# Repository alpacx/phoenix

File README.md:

# Phoenix — gateway multi-piattaforma

Gateway sperimentale, non ancora un prodotto validato. Backend ESP32 esistente;
backend Linux per ROCK 4C+ implementato in forma sperimentale e testato in Docker. La sezione hardware/build sotto descrive
ESP32; per Linux consultare il relativo README e le verifiche disponibili.

## Organizzazione

- [ESP32 / ESP-IDF](platforms/esp32/README.md): sorgenti in `platforms/esp32/main/`.
- [Linux / ROCK](platforms/linux/README.md): backend Linux, istruzioni e stato delle verifiche.
- `shared/web/`: pannello amministrativo comune.
- `shared/phoenix_core/`: logica C portabile.
- [Mappa del progetto](docs/PROJECT_STRUCTURE.md) e [istruzioni agenti](AGENTS.md).
- `hardware/phoenix-g1/`: progettazione della scheda custom, ancora incompleta.

Implementati: Ethernet IP101/RMII con DHCP, USB HS CDC-NCM con DHCP/NAT IPv4,
firewall L3/L4, API amministrativa locale e pannello, importatore WireGuard IPv4
full tunnel e blocco in uscita, gestione C6 STA/AP e aggiornamento firmato in software. La presenza del codice e una build riuscita non
provano il funzionamento sul banco: consultare PROGRESS.md.

## Build

ESP-IDF 5.5.4, commit esatto `10ca0dff2f40aeb539f22d1ef88d031cf7421743`.
Dipendenze registry e relativi hash in dependencies.lock. Toolchain installata:
`riscv32-esp-elf esp-14.2.0_20260121`. Script configurato per l'ambiente locale;
IDF_PATH e IDF_PYTHON_ENV_PATH sono sovrascrivibili.

```sh
./tools/test.sh
# Scheda rilevata v3.1; USB dati spento:
./tools/build.sh -B build-rev3 -D SDKCONFIG=build-rev3/sdkconfig \
  -D 'SDKCONFIG_DEFAULTS=sdkconfig.defaults;sdkconfig.rev3'
# Solo compilazione del percorso USB, NON certifica il cablaggio:
./tools/build.sh -B build-usb-rev3 -D SDKCONFIG=build-usb-rev3/sdkconfig \
  -D 'SDKCONFIG_DEFAULTS=sdkconfig.defaults;sdkconfig.rev3;sdkconfig.lab;sdkconfig.signed'
```

La variante firmata richiede prima la chiave descritta in [OTA](docs/OTA.md).

Il default sdkconfig.defaults supporta P4 v1.x; non caricarlo sulla v3.1.
Per una build USB di banco v3.x aggiungere sdkconfig.lab DOPO sdkconfig.rev3
in una cartella di build nuova. Non modificare i file SDK globali.

## Cablaggio e flash

Leggere [HARDWARE.md](docs/HARDWARE.md). La USB-C è seriale/alimentazione; la
Type-A è OTG e porta VBUS generata dalla scheda. Non collegare un generico
cavo host-host. USB dati resta disattivata per default.

Il backup originale è locale, riservato e ignorato da Git:
`results/recovery/original-flash.bin`. Non distribuirlo: può contenere dati
preesistenti. Per ripristinare, dopo aver identificato nuovamente la stessa
scheda e verificato hash/dimensione:

```sh
# Da ambiente ESP-IDF attivato. PORT deve essere la P4 dedicata identificata.
python -m esptool --chip esp32p4 --port "$PORT" write_flash 0 results/recovery/original-flash.bin
```

Non modificare eFuse. Nessuna flash encryption/secure boot irreversibile attivata.
BOOT+RESET è la via ROM di recupero; BOOT condivide GPIO35 con Ethernet TXD1:
non usarlo come pulsante dell'interfaccia durante il traffico.

## Uso sperimentale

USB LAN: 192.168.7.1/24, DHCP, pannello http://192.168.7.1/. Nessun servizio
amministrativo accettato dall'uplink. Pairing via UART nei primi 120 secondi:
`pair ` seguito da 64 caratteri esadecimali casuali, mai riportati nei log.
Il token rimane solo nel client; la scheda conserva SHA-256 in NVS.
`time <epoch UNIX di 10 cifre>` imposta l'orologio nello stesso intervallo.
Il pannello conserva il token nella sessionStorage della scheda browser e lo elimina al logout.

All'avvio il traffico inoltrato è bloccato. La modalità diretta è una scelta
esplicita via API. WireGuard resta chiuso finché non esiste una sessione valida.
Il dispositivo non controlla il traffico del Mac sulle altre interfacce.
Non è un antivirus, un IDS completo o uno strumento di ispezione HTTPS.

[API](docs/API.md) · [Architettura](docs/ARCHITECTURE.md) ·
[Prove](docs/TESTING.md) · [Dipendenze](docs/DEPENDENCIES.md) ·
[Attività](TASKS.md) · [Ripresa](NEXT_SESSION.md)

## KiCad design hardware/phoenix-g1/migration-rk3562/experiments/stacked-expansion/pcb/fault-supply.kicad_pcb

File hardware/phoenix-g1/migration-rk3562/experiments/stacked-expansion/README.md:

# Espansione sovrapposta — sostituzione J3

Stato: **schema integrato, piazzamento e blocco locale di protezione parzialmente instradati e verificati**.
Il derivato corrente è indicato da `working-candidate.json`.
Non pronto per fabbricazione. Il checkpoint precedente `../lpddr4-1gb/working-board.json`
resta immutato; questo candidato va completato prima di promuoverlo.

## Fissaggi obbligatori — riserva CAD

Aprire `mechanical/mounting-reservations.kicad_pcb`, layer **Dwgs.User**:
H8101 (53;4) e H8102 (83;3) mm, due posizioni asimmetriche rispetto a J3.
Cerchio interno: futuro foro NPTH 2,2 mm per M2; esterno: riserva 5,4 mm
su entrambi i lati per testa vite/distanziale e margine. Distanza PCB nominale
3,5 mm, da abbinare alle tolleranze DF40; nessun distanziale commerciale
ancora selezionato. La coppia di fori da sola non certifica l'anti-inversione.

**Non sono fori già realizzati**: l'overlay segnala le riserve e non genera
forature. Per liberarle vanno ricollocati C422/C425/R1811 presso H8101 e
C445/C470/L405/R431 presso H8102. Nessuna pista/via esistente attraversa
le riserve nella verifica geometrica attuale. Zone rame da tenere escluse
quando si creeranno i fori. `mechanical/mounting-interface.json` registra
questi blocchi: risolverli è obbligatorio prima del rilascio e prima di
progettare la figlia. Riconvalidare tutto nel passaggio a 85×35 mm.
Rigenerare l'overlay con `tools/reserve_stacked_mounts.py` dopo ogni
variazione del candidato. Il PCB elettrico precedente resta invariato.

## Scelta e posizione

J3 sostituisce il precedente PZ127 2×10: non aggiunge un secondo connettore.
Base Hirose DF40C-40DP-0.4V(51), JLC C424643; controparte sulla futura
scheda accessoria DF40HC(3.5)-40DS-0.4V(51), JLC C3020022.
40 contatti a passo 0,4 mm, distanza nominale tra PCB 3,5 mm.
Corpo base 9,52×2,97 mm; courtyard 10,1×3,9 mm.
Centro sul PCB: (67,5; 2,5) mm, lato superiore, vicino a Ethernet.
Tre condensatori non instradati (C423/C431/C435) passano al retro alle stesse
coordinate. La qualità del loro futuro collegamento di alimentazione resta da verificare.
Il PCB candidato conserva **90×40 mm**; il target **85×35 mm** non è ancora validato.

Il connettore non è polarizzato: servono fissaggi asimmetrici o una chiave
meccanica. La scheda figlia deve evitare il corpo RJ45 e lasciare spazio al
raffreddamento passivo; 3,5 mm NON autorizzano una scheda piena sopra tutti i
componenti. Sagoma, fissaggi, altezza totale e assemblabilità da verificare.

## Interfaccia

`pinout.json` definisce la numerazione custom Phoenix, non uno standard HAT.
USB 2 host dedicata RK3562: AE26 DM e AE27 DP; USB-C device invariata.
Sono disponibili I2C, UART, SPI e quattro GPIO a logica 3,3 V.
GPIO0 abilita l'alimentazione; GPIO1 legge il fault. Due contatti restano NC.
Il modem, la eSIM, i regolatori e l'eventuale adattamento livelli sono sulla
scheda accessoria futura: non sono inclusi in questo progetto.

Otto contatti portano +5V_ADDON, ma la corrente nominale di 0,3 A per contatto
non dimostra un budget di sistema di 2,4 A. Il ramo TPS259531 è disabilitato
all'avvio tramite pull-down e ha un limite preliminare di circa 0,99 A.
Il budget USB d'ingresso deve alimentare anche tutta la scheda base: non è
ancora dimostrato che basti per un modem LTE, soprattutto nei picchi.
Non collegare a caldo e non alimentare esternamente la scheda accessoria.
MP1–MP4 sono soli ancoraggi meccanici. La controparte richiede verifica della
corrispondenza speculare dei contatti prima del layout della scheda figlia.

## Evidenze e costi

Snapshot JLC in `sourcing/`, osservati il 13 novembre 2026:
- C424643: canPresaleNumber 12913, prezzo iniziale 0,5367 USD.
- C3020022: canPresaleNumber 1991, prezzo iniziale 1,1518 USD.
Totale indicativo coppia 1,6885 USD; non include PCBA, spedizione, imposte,
protezione di alimentazione né scheda figlia. I campi di stock non si sommano
tra loro e non garantiscono disponibilità immediata per un ordine PCBA.

Dimensioni dal catalogo Hirose locale `hirose-df40-catalog.pdf`, pagine 7 e 10;
[scheda ufficiale base](https://www.hirose.com/en/product/p/CL0684-4013-7-51).
Footprint con numerazione Phoenix: da qualificare con i componenti reali.
La regola DRC da 0,17 mm vale SOLO fra pad dello stesso J3 (passo 0,4 mm,
land 0,23 mm), senza ridurre la clearance generale.

`audit.json`: 71 disposizioni pin schema/PCB verificate; 2460 segmenti/via
preservati; UUID distinti; reti originali invariate salvo i due pin host prima NC.
DRC: nessun corto/clearance/courtyard aggiuntivo; restano 125 via dangling e
14 problemi serigrafia preesistenti. 499 elementi non connessi riportati:
possibile limite di report, non misura del totale residuo.
ERC: 15 power_pin_not_driven e una isolated_pin_label; NON pulito.

## Lavoro ancora necessario

Instradare USB host a impedenza controllata e ramo di alimentazione; qualificare
protezione ESD, dissipazione e picchi del modem; assegnare MPN ai passivi nuovi
ed aggiornare disponibilità del ramo di potenza. Integrare separatamente eMMC,
display e comando, poi compattare sul target. Progettare controparte, chiave
meccanica e fissaggi prima di ordinare. Nessuna simulazione SI/PI o prova fisica.

## Riproduzione

1. `tools/build_stacked_expansion.py` con Python + sexpdata.
2. Esportare `system/kicad/integrated/phoenix-g1.kicad_sch` con KiCad CLI
   `sch export netlist --format kicadxml` in `system/review/netlist.xml`.
3. `tools/place_stacked_expansion.py` con Python KiCad pcbnew.
4. KiCad CLI `pcb drc --format json` in `pcb/drc.json` e
   `sch erc --format json` in `system/review/erc.json`.
5. `tools/audit_stacked_expansion.py` con Python KiCad pcbnew.

Gli script riscrivono solo questa directory candidata; non il PCB sorgente.

## Riserve ausiliarie H8103–H8105

Aggiunti tre punti M2 provvisori, oltre ai due della scheda figlia, nel medesimo
overlay `mechanical/mounting-reservations.kicad_pcb` (Dwgs.User).
La mappa `mechanical/mounting-overview.svg` mostra la distribuzione proposta.
- H8103 (21;3): staffa/case lato USB.
- H8104 (37;31): possibile staffa per dissipazione; interferisce con clock,
  test point e condensatori. Priorità all'integrità elettrica: spostare la
  riserva anziché il clock se il successivo layout lo richiede.
- H8105 (70;34): appoggio staffa/case lato Ethernet.

Riserve da 5,4 mm, futuro NPTH 2,2 mm; nessuna foratura reale introdotta.
21 riferimenti interferiscono con le tre nuove riserve, censiti nel JSON.
Il controllo geometrico non trova piste/via nelle riserve, ma le zone rame
non sono escluse e le quote devono essere riconvalidate dopo la compattazione.
Non è un fissaggio diretto standard per una ventola: servirebbe una staffa
adattatrice. Non è stato aggiunto un circuito elettrico per alimentarla.
Raffreddamento passivo prioritario. Evitare carico concentrato sul BGA,
verificare flessione PCB, pressione del thermal pad, isolamento e accesso viti.
I 3,5 mm della scheda figlia non definiscono l'altezza delle staffe ausiliarie.

## Avanzamento collegamenti locali — checkpoint corrente

Ripartire da `working-candidate.json`: `pcb/logic-reference.kicad_pcb`, verificato
in `pcb/logic-reference-audit.json`. Il PCB principale LPDDR4 rimane invariato.

- Riposizionati i sei passivi U8101, senza cambiare netlist o componenti.
- Tutte e quattro le reti locali ILIM/dVdt/EN/fault collegate ai rispettivi
  passivi; dVdt accorciata da 7,79 a 2,83 mm.
- Sette pad GND collegati al piano esistente, continuità verificata fino a
  U4.69; altri pin GND del PMIC restano incompleti nel progetto generale.
- Collegati i due pin IN al condensatore di ingresso e OUT al condensatore
  di uscita. Tracce locali 0,3 mm: non è una qualifica di portata/temperatura.
- R8102.2 collegata alla linea +3V3_IO U4.55 con un nuovo via e percorso
  interno In2.Cu. Continuità verificata, 14,81 mm nominali di percorso.
- 2460 piste/via originali preservati, 114 nuovi segmenti/via nel derivato.
- DRC invariato: 125 via dangling e 14 difetti serigrafia preesistenti,
  nessun nuovo corto/clearance/courtyard. 499 airwire riportati, conteggio
  potenzialmente limitato. Non significa completamento della scheda.

Restano alimentazione d'ingresso del ramo, uscita verso J3, GPIO fino al SoC,
coppia USB, budget energetico e qualifica elettrica/termica. I fissaggi
restano riserve non liberate; eMMC/display/comando e compattazione sono aperti.
I render precedenti non rappresentano questo ultimo piazzamento.

Catena riproducibile (Python KiCad): `route_stacked_control.py`,
`route_stacked_ground.py` (con --input/--output/--report),
`route_stacked_local_power.py`, `route_stacked_fault_supply.py`.
Eseguire DRC sul risultato e `audit_stacked_local_power.py fault-supply`.
Gli output intermedi mantengono i rispettivi limiti e non sono checkpoint finali.

Il tentativo `mechanical/mount-clearance-trial.kicad_pcb` è SCARTATO:
spostava troppo lontano alcuni passivi di potenza e non liberava due componenti.
Non usarlo come base di routing. Le riserve restano nel relativo overlay.

## Vincoli USB e fabbricazione

La [guida ufficiale JLCPCB](https://jlcpcb.com/help/article/user-guide-to-the-jlcpcb-impedance-calculator),
consultata il 13 novembre 2026, lega il calcolo a stack-up, strato, riferimento,
rivestimento e geometria. Il record JLC06161H-3313 del progetto è ancora un
candidato: non definisce larghezza/gap USB qualificati. Il tentativo di usare
il calcolatore interattivo è impedito dal browser host non disponibile in
questa sessione. Non sono stati inventati o applicati valori di impedenza.

## Avanzamento successivo: alimentazione e controlli fino a J3

Il derivato `logic-reference` completa geometricamente:
- ingresso eFuse dalla rete +5V_MAIN esistente;
- uscita eFuse agli otto contatti +5V_ADDON di J3;
- quattordici contatti GND J3 al piano esistente;
- abilitazione e fault U1.K2/U1.L3 ↔ J3.27/J3.28 ↔ eFuse;
- riferimento +3V3_IO al contatto J3.36.

R8102 ora ruotata di 180° per separare l'uscita fault dal suo pull-up.
747 segmenti/via nuovi rispetto al candidato originario; tutti i 2460
precedenti preservati. DRC resta alle stesse 139 violazioni preesistenti.
Collegamento non equivale a qualifica di portata: alimentazione interna
1 mm su In3, colli esterni 0,3 mm, via 0,6/0,3 mm e dita J3 0,15 mm sono
candidati con verifica termica/caduta/tolleranze e budget USB ancora aperti.
La corrente nominale del limite di protezione non è un budget di carico LTE.

Regole aggiunte, esplicite nei .kicad_dru: 0,17 mm di clearance solo contro
pad J3; 0,15 mm di larghezza minima per dita +5V_ADDON; 0,0762 mm per
escape GPIO dal BGA. Le piste lontane dal connettore conservano 0,20 mm di
clearance. Escape BGA vincolati al processo sperimentale già usato dalla DDR:
nessuna qualifica di fabbricazione o integrità del segnale implicita.
Istruzioni precedenti che descrivono feed/GPIO aperti sono storiche.

## Riserve meccaniche applicate al rame

`protect_stacked_mounts.py` genera `pcb/mount-protected.kicad_pcb` da cui
riparte la catena di routing. H8101–H8105 sono rule area su tutti e sei gli
strati: vietati nuove piste, via e riempimenti. I componenti che occupano
le riserve sono ancora da ricollocare; i fori non sono creati. Le rule area
non vietano pad/footprint esistenti, per distinguere quel lavoro irrisolto
dalla protezione del nuovo routing.

Il checkpoint `logic-reference` è stato rigenerato con tali zone: tutti i
controlli end-to-end passano, DRC invariato. Nel piazzamento aggiornato C8103
è (79;4,2) mm/180°, R8103 (82,5;9,5) mm/0°, R8102 (73;6,5) mm/180°.
Il report JSON attuale prevale sui conteggi e sulle coordinate storiche.

`tools/rebuild_stacked_expansion.py` ricostruisce i passaggi in sequenza,
interrompendosi su fallimento del tool o nuove violazioni DRC; promuove il
checkpoint solo dopo la verifica di tutte le connessioni richieste e delle
cinque riserve. Lo stadio intermedio output-bus ammette un via dangling
aggiuntivo, che deve scomparire allo stadio output-feed.

`tools/route_stacked_aux_io.py` è un esperimento separato: ogni rete viene
accettata soltanto dopo continuità e DRC; le altre vengono scartate. Non
qualifica SPI/UART/I2C né il processo delle piste BGA a 3 mil, e non
completa la coppia USB. L'audit finale deve precedere la promozione.

## Checkpoint 13 novembre — segnali ausiliari e riserve meccaniche

Il puntatore `working-candidate.json` ora seleziona `pcb/aux-io.kicad_pcb`.
L'audit preserva tutte le 2.460 piste/via originali e le reti dei pad; aggiunte
1.591 primitive, non 1.591 reti. Le 139 violazioni DRC preesistenti sono invariate.
Cinque riserve meccaniche impediscono nuove piste/via/riempimenti, ma non sono
fori reali e contengono ancora componenti da riposizionare.

Alimentazione protetta, masse, riferimento logico e GPIO enable/fault sono
collegati. Dei segnali aggiuntivi risultano collegati SCL, SPI_CLK, MOSI, CS0.
SDA, MISO, CS1, UART TX/RX e GPIO2/3 restano aperti; USB non instradata.
I tentativi `aux-io-second` e `aux-io-fine` non hanno aggiunto percorsi e non
sostituiscono il checkpoint. La ricerca limitata non dimostra impossibilità
fisica: occorre rivedere il fanout completo del connettore, evitando di occupare
prima i corridoi necessari ai pad adiacenti.

`rebuild_stacked_expansion.py` ricostruisce fino a `logic-reference` e riporta
il puntatore a quel livello. Per riprodurre lo stadio successivo eseguire
`route_stacked_aux_io.py`, quindi `audit_stacked_local_power.py aux-io` con
Python KiCad; promuovere soltanto dopo controllo del report e SHA.
Il candidato eMMC è separato in `../emmc-system`: schema aggiornato, PCB ancora
con NOR. Non utilizzare netlist e PCB dei due candidati come coppia di produzione.

Studio meccanico `mechanical/mount-local-trial.json`: ricerca di spostamenti
entro 4 mm sullo stesso lato; solo R1811 trova una posizione libera, senza nuovi
DRC. Gli altri sei componenti presso H8101/H8102 richiedono una revisione locale
più ampia. Studio non promosso; nessun foro creato.

Il tentativo `aux-io-wide` non è promosso: nella versione sperimentale del
selettore di strato mancava In3 dalla verifica delle via. Il DRC ha respinto
il percorso e preservato il checkpoint; il generatore ora verifica sempre
i sei strati distinti, indipendentemente dallo strato di routing scelto.

## Inventario senza limite del report DRC

`inventory_stacked_connectivity.py` usa la connettività dei pad, senza affidarsi
al limite degli elementi mostrati dal DRC. Sul checkpoint aux-io: 276 reti,
269 reti con più pad,231 reti ancora suddivise in gruppi. GND ha 582 pad e 471 gruppi.
Il report è `pcb/connectivity-inventory.json`, legato allo SHA del PCB.
Questi numeri non sono percentuali di completamento né qualifiche elettriche.

Anche i tentativi conclusivi `aux-io-back` e `aux-io-small-via` non hanno
aggiunto reti: il secondo usa via 0,45/0,20 mm entro le regole esistenti.
L'audit finale conferma il checkpoint precedente, senza nuove violazioni.
Non ripetere questi tentativi invariati: occorre modificare la disposizione
delle uscite del connettore o il relativo fanout, poi ripetere i controlli.

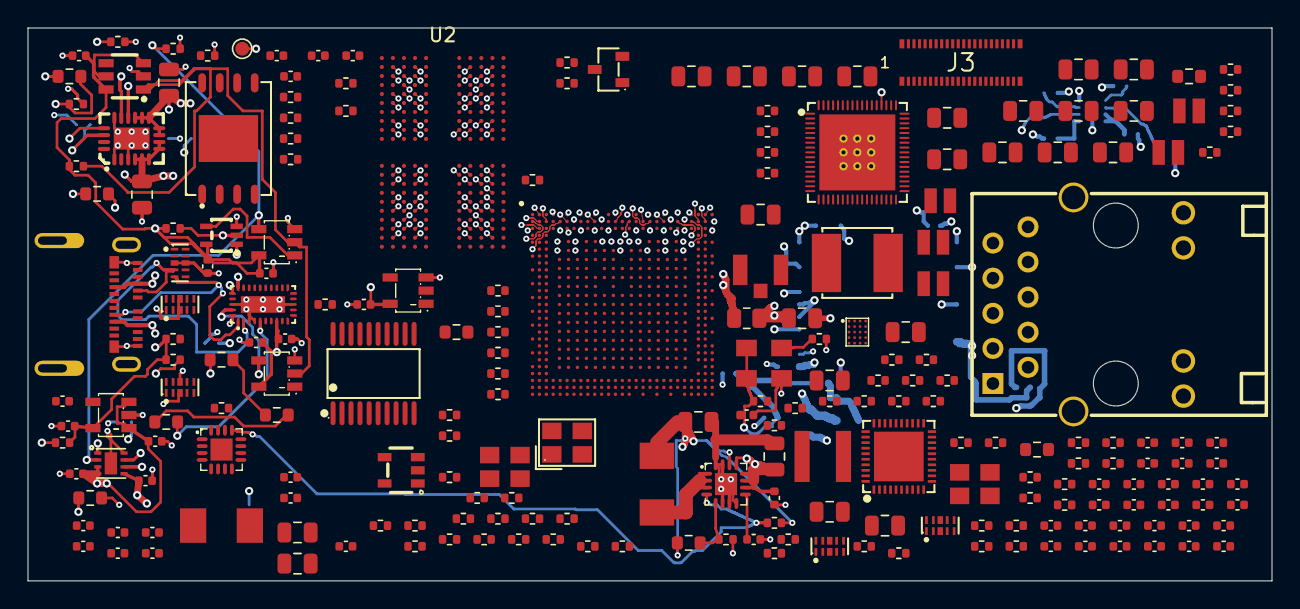
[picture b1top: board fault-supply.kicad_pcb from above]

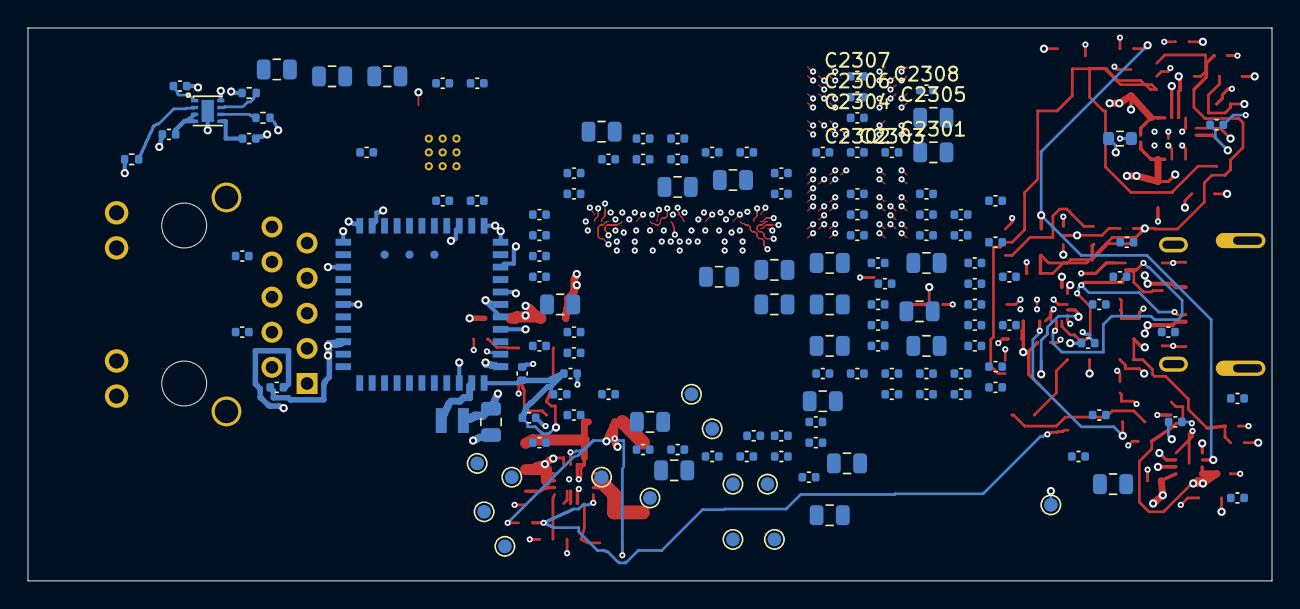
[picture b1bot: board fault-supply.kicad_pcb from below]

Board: 6 copper layers, 90.0 x 40.0 mm, 362 parts (141 on the bottom side), 268 nets.

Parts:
C410, C411, C412, C451, C452, C454, C501, C512, C513, C514, C516, C517, C518, C522, C1103, C1104, C1105, C1106, C1107, C1401, C1503, C1811, C2007, C2302, C2303, C2304, C2306, C2307, C2308: 100n; C_0402_1005Metric
C413, C414, C415, C519, C1402, C8101, C8102: 1u; C_0402_1005Metric
C421, C422, C423, C424, C425, C431, C432, C433, C434, C435, C441, C442, C443, C444, C445, C1304, C1305, C1603, C1604, C1605, C1606, C1607, C1608, C1613, C1614, C1618, C1619, C1622, C1623, C2204: 22u / 10V; C_0805_2012Metric
C460, C461, C462, C463, C464, C465, C466, C467, C468, C469, C480, C481, C482, C483, C484, C485, C531, C1101, C1201, C1203, C1611, C1612, C1626, C1628, C1630, C1632, C1634, C1636, C1680, C1682, C1801, C1812, C2005: 1u / 10V; C_0402_1005Metric
C470, C1301, C1615, C1620, C1624, C1650, C1664, C1678, C2201: 10u / 10V; C_0805_2012Metric
C511, C515: 4.7u; C_0402_1005Metric
C520, C521, C1501, C1502: 20p C0G / tune; C_0402_1005Metric
C601, C602, C603, C604, C605: 100n / 16V X7R; C_0402_1005Metric
C606: 100n / 10V X7R; C_0402_1005Metric
C1001, C1002, C1011, C1012, C1013, C1014: 22u / 10V X5R; C_0805_2012Metric
C1020: 1u / 10V X5R; C_0402_1005Metric
C1102, C1802: 2.2u / 10V; C_0402_1005Metric
C1202: 22n / 10V; C_0402_1005Metric
C1302, C1601, C1609, C1616, C1621, C1625, C1627, C1629, C1631, C1633, C1635, C1637, C1638, C1639, C1640, C1641, C1642, C1643, C1644, C1645, C1646, C1647, C1651, C1652, C1653, C1654, C1655, C1656, C1657, C1658, C1659, C1660, C1661, C1662, C1665, C1666, C1667, C1668, C1669, C1670, C1671, C1672, C1673, C1674, C1675, C1676, C1679, C1681, C1683: 100n / 10V; C_0402_1005Metric
C1303: 10n / 10V; C_0402_1005Metric
C1602, C1610, C1617, C1648, C1649, C1663, C1677: 4.7u / 10V; C_0402_1005Metric
C1901, C1902: 1u / 25V X7R; C_0805_2012Metric
C1903: 1n / C0G; C_0402_1005Metric
C2001: 22u / 6.3V; C_0805_2012Metric
C2002, C2006, C2202: 100n / 16V; C_0402_1005Metric
C2003: 4.7u / 6.3V; C_0805_2012Metric
C2004: 4.7u / 6.3V; C_0402_1005Metric
C2008, C2009: 8p C0G; C_0402_1005Metric
C2203: 1n / 10V; C_0402_1005Metric
C2301, C2305: 10u; C_0805_2012Metric
C8103: 22n; C_0402_1005Metric
FB2001: 100R @100MHz / 4A; R_0805_2012Metric
J1: 2012670005; USB_C_Molex_2012670005
J2: HR911130A; RJ45-TH_HR911130A
J3: DF40C-40DP-0.4V(51); DF40C_40DP_0.4V
J2001: U.FL-R-SMT-1; Hirose_UFL_R_SMT_1_80
L401, L402, L403, L404, L405: 470nH; L_APH201610
L501: 2.2uH DCR39m max; L_ANR4030
L1001: 240nH - candidate; IND-SMD_L5.0-W5.0-PRS5020-330MT
L1301, L2201: 2.2uH DCR35m max; L_APH0518
L2001: 2.2uH / 2.4A Isat at 20C; Murata_DFE201610E
Q1: MMBT3904-C20526; SOT-23-3_L2.9-W1.3-P1.90-LS2.4-BR
R201: 240R 1%; R_0402_1005Metric
R410: 180k 1%; R_0402_1005Metric
R411, R1505, R2203: 100k 1%; R_0402_1005Metric
R412, R413, R516, R1402, R1403, R1404, R1504, R2002: 10k; R_0402_1005Metric
R414, R415, R501, R502, R503, R504, R505, R506, R507, R508, R509, R510, R511, R512, R515, R1401, R1501, R2003: 22R; R_0402_1005Metric
R416, R417: 2.2k; R_0402_1005Metric
R421, R422, R424, R2004: 100R; R_0402_1005Metric
R431: 45.3k 0.1%; R_0603_1608Metric
R432: 121k 0.1%; R_0603_1608Metric
R513: 2.49k 1%; R_0402_1005Metric
R514: 1.8k; R_0402_1005Metric
R521, R522, R523, R524, R525, R526, R527, R528, R529, R2101, R2102: 4.7k; R_0402_1005Metric
R530: 0R - power link; R_0402_1005Metric
R601, R605, R606: 300k 0.1% 25ppm; R_0603_1608Metric
R602, R603, R604: 200k 1%; R_0402_1005Metric
R1001: 100R 1%; R_0402_1005Metric
R1002: 51k 1%; R_0402_1005Metric
R1101, R1103, R1202, R1301, R1804, R2201, R8102, R8103: 100k; R_0402_1005Metric
R1102, R1802, R1811, R1812, R1813, R1814, R1815, R2010, R2011, R2012, R2013, R2014, R2103, R2104: 47k; R_0402_1005Metric
R1201: 806R 1%; R_0603_1608Metric
R1502: 1M; R_0402_1005Metric
R1503: 120R 1%; R_0402_1005Metric
R1506: 1M 1%; R_0402_1005Metric
R1507: 0R; R_0402_1005Metric
R1601, R1602: 0R supply link; R_0402_1005Metric
R1801: 1k; R_0402_1005Metric
R1803: 180R 1%; R_0603_1608Metric
R1901: 35.7k 0.1% 25ppm; R_0603_1608Metric
R1902, R1904: 10k 0.1% 25ppm; R_0402_1005Metric
R1903: 47.5k 0.1% 25ppm; R_0603_1608Metric
R1905: 33.2k 1%; R_0603_1608Metric
R2001: 0R RF tuning; R_0402_1005Metric
R2202: 348k 1%; R_0603_1608Metric
R8101: 2.1k candidate; R_0402_1005Metric
TP1: GND; TestPoint_Pad_D1.0mm
TP2: VBUS_RAW; TestPoint_Pad_D1.0mm
TP3: +5V_MAIN; TestPoint_Pad_D1.0mm
TP4: +3V3_SYS; TestPoint_Pad_D1.0mm
TP5: +3V3_PMU; TestPoint_Pad_D1.0mm
TP6: +3V3_IO; TestPoint_Pad_D1.0mm
TP7: +1V5_DDR; TestPoint_Pad_D1.0mm
TP8: VDD_CPU; TestPoint_Pad_D1.0mm
TP9: RESET_N; TestPoint_Pad_D1.0mm
TP10: RECOVERY_ADC; TestPoint_Pad_D1.0mm
TP11: DEBUG_RX; TestPoint_Pad_D1.0mm
TP12: DEBUG_TX; TestPoint_Pad_D1.0mm
TP13: USB_POWER_FAULT_N; TestPoint_Pad_D1.0mm
TP14: SYS_3V3_PG; TestPoint_Pad_D1.0mm
U1: RK3562; RK3562_FCCSP478_13.9mm_MIXED_PITCH_CANDIDATE
U2: H9HCNNN8KUMLHR-NME; H9HCNNN8KUMLHR_FBGA200_10x15_P0.8x0.65_DRAFT
U4: RK809-5; QFN-68_L7.0-W7.0-P0.35-BL-EP5.5
U5: RTL8211F-CG; WQFN-40_L5.0-W5.0-P0.4-BL-EP
U6: HD3SS3220IRNHR; WQFN-30_L4.5-W2.5-P0.4-BL-EP
U7, U8, U9: TPD4EUSB30DQAR; USON-10_L2.5-W1.0-P0.50-BL
U10: RK860-0; WLCSP-20_L2.0-W1.6-R5-C4-P0.40-TL
U11: TLV75533PDBVR; SOT-23-5_L3.0-W1.7-P0.95-LS2.8-BR
U12: TPS3808G33DBVR; SOT-23-6_L2.9-W1.6-P0.95-LS2.8-BR
U13, U16: SN74LVC1G04DBVR; SOT-23-5_L3.0-W1.7-P0.95-LS2.8-BR
U14: SN74LVC1G02DCKR; SC-70-5_L2.1-W1.3-P0.65-LS2.1-BR
U15, U8101: TPS259531DSGR; WSON-8_L2.0-W2.0-P0.50-TL-EP
U17: TPS62132RGTR; VQFN-16_L3.0-W3.0-P0.50-TL-EP
U18: W25Q256JVEIQTR; WSON-8_L8.0-W6.10-P1.27-BL-EP
U19: SN74LVC1G08DBVR; SOT-23-5_L3.0-W1.7-P0.95-LS2.8-BR
U20: TPS7A2030PDBVR; TSOT-23-5_L2.9-W1.6-P0.95-LS2.8-BR
U21: SN74LVC541APWR_C113281; TSSOP-20_L6.5-W4.4-P0.65-LS6.4-BL
U22, U23: TPD4E05U06DQAR; USON-10_L2.5-W1.0-P0.50-BL
U24: TPS25940ARVCR; WQFN-20_L4.0-W3.0-P0.50-BL-EP
U25: AP6256; AP6256_12x12_P0.9
U26: TPS62130RGTR; VQFN-16_L3.0-W3.0-P0.50-TL-EP
Y1: 24MHz CL12pF ESR40R; Crystal_3225_JWT
Y501: 25MHz CL12pF; Crystal_3225_YXC
Y2001: OVETDLJANF-32.768KHZ; Taitien_OV_5032
Y2002: X1E0000210877; CRYSTAL-SMD_4P-L3.2-W2.5-BL

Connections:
+1V0_PHY: C511.1, C512.1, C513.1, C514.1, C522.1, L501.2, U5.3, U5.8, U5.21, U5.38
+1V1_LPDDR4: C433.1, C443.1, C1646.1, C1647.1, C1648.1, C1649.1, C1650.1, C1651.1, C1652.1, C1653.1, C1654.1, C1655.1, C1656.1, C1657.1, C1658.1, C1659.1, C1660.1, C1661.1, C1662.1, C1663.1, C1664.1, C1665.1, C1666.1, C1667.1, C1668.1, C1669.1, C1670.1, C1671.1, C1672.1, C1673.1, C1674.1, C1675.1, C1676.1, C1677.1, C1678.1, L403.2, R201.2, R431.1, R1503.2, TP7.1, U1.1D6, U1.1D11, U1.1E3, U1.1E4, U1.1E5, U1.1E6, U1.1E7, U1.1E8, U1.1E9, U1.1E10, U2.A4, U2.A9, U2.AA3, U2.AA5, U2.AA8, U2.AA10, U2.AB4, U2.AB9, U2.B3, U2.B5, U2.B8, U2.B10, U2.D1, U2.D5, U2.D8, U2.D12, U2.F3, U2.F5, U2.F8, U2.F10, U2.G2, U2.H1, U2.H5, U2.H8, U2.H12, U2.K1, U2.K3, U2.K10, U2.K12, U2.N1, U2.N3, U2.N10, U2.N12, U2.R1, U2.R5, U2.R8, U2.R12, U2.T2, U2.U3, U2.U5, U2.U8, U2.U10, U2.W1, U2.W5, U2.W8, U2.W12, U4.26
+1V8_SYS: C435.1, C445.1, C2301.1, C2302.1, C2303.1, C2304.1, C2305.1, C2306.1, C2307.1, C2308.1, L405.2, U2.F1, U2.F12, U2.G4, U2.G9, U2.T4, U2.T9, U2.U1, U2.U12, U4.59
+3V0_LCD: C1802.1, C1811.1, C1812.1, U20.5, U21.20
+3V3_AON: C606.1, C1102.1, C1103.1, C1104.1, C1105.1, C1106.1, C1107.1, R602.1, R603.1, R604.1, R1101.1, R1202.2, U6.8, U11.5, U12.3, U12.5, U12.6, U13.5, U14.5, U16.5, U19.5
+3V3_IO: C470.1, C1401.1, C1402.1, C1627.1, C1628.1, C1637.1, C1638.1, C1639.1, C1640.1, C1641.1, C1683.1, C2004.1, C2005.1, C2006.1, C2007.1, J3.36, R530.1, R1402.2, R1403.2, R1404.2, R1505.1, R1804.1, R1815.2, R2010.2, R2011.2, R2012.2, R2013.2, R2014.2, R2101.2, R2102.2, R8102.2, TP6.1, U1.1F14, U1.1G15, U1.1H14, U1.1K3, U1.1L3, U1.1L5, U1.1M4, U1.1M14, U4.55, U18.8, U20.3, U25.22, Y2001.1, Y2001.4
+3V3_PHY: C515.1, C516.1, C517.1, C518.1, C519.1, R514.2, R521.2, R525.2, R526.2, R527.2, R530.2, U5.11, U5.28, U5.29, U5.40
+3V3_PMU: C465.1, C1625.1, C1626.1, R412.1, R413.1, R416.1, R417.1, R1002.1, R2103.2, R2104.2, TP5.1, U1.1L11, U1.1L12, U4.31
+3V3_SD: C469.1, U4.58
+3V3_SYS: C421.1, C422.1, C423.1, C424.1, C425.1, C480.1, C481.1, C482.1, C483.1, C484.1, C485.1, C1304.1, C1305.1, L1301.2, R410.1, R1301.2, TP4.1, U4.4, U4.10, U4.11, U4.22, U4.24, U4.30, U4.33, U4.45, U4.54, U4.57, U4.66, U17.14
+3V58_WIFI: C2204.1, FB2001.1, L2201.2, R2201.2, R2202.1, U26.14
+5V_ADDON: C8102.1, J3.1, J3.2, J3.3, J3.4, J3.5, J3.6, J3.7, J3.8, U8101.5
+5V_MAIN: C1001.1, C1002.1, C1203.1, C1301.1, C1302.1, C1801.1, C2201.1, C2202.1, C8101.1, R1803.1, TP3.1, U10.D1, U10.D2, U10.E1, U10.E2, U15.5, U17.10, U17.11, U17.12, U20.1, U26.10, U26.11, U26.12, U26.13, U8101.3, U8101.4
ADDON_DVDT: C8103.1, U8101.1
ADDON_ILIM: R8101.1, U8101.7
ADDON_USB_DM: J3.21, U1.AE26
ADDON_USB_DP: J3.19, U1.AE27
AON_READY: R1101.2, U12.1, U13.2, U19.2
CC_OUT1_N: R603.2, U6.25, U14.1
CC_OUT2_N: R604.2, U6.26, U14.2
CC_VBUS_SENSE: R606.2, U6.5
CC_VBUS_SERIES_1: R601.2, R605.1
CC_VBUS_SERIES_2: R605.2, R606.1
CHASSIS: J2.P10, J2.SHIELD0, J2.SHIELD1
CPU_BUCK_EN: R1002.2, U10.A2
CPU_FB_SENSE: C1020.2, R1001.2, U10.A4
CPU_SW: L1001.1, U10.D3, U10.D4, U10.E3, U10.E4
DDR_FB: R431.2, R432.1, U4.27
DDR_RZQ: R1503.1, U1.1D4
DEBUG_RX: TP11.1, U1.AF20
DEBUG_TX: TP12.1, U1.AE20
ETH_CENTER_TAP: C531.1, J2.P1
ETH_MDC: U1.AC1, U5.13
ETH_MDI0_N: J2.P3, U5.2, U22.2
ETH_MDI0_P: J2.P2, U5.1, U22.1
ETH_MDI1_N: J2.P7, U5.5, U22.5
ETH_MDI1_P: J2.P4, U5.4, U22.4
ETH_MDI2_N: J2.P6, U5.7, U23.2
ETH_MDI2_P: J2.P5, U5.6, U23.1
ETH_MDI3_N: J2.P9, U5.10, U23.5
ETH_MDI3_P: J2.P8, U5.9, U23.4
ETH_MDIO: R514.1, U1.AC2, U5.14
ETH_RESET_GPIO_N: R515.1, U1.T2
ETH_RXCLK: R512.1, U1.U2
ETH_RXD0: R507.1, U1.W3
ETH_RXD1: R508.1, U1.W1
ETH_RXD2: R509.1, U1.W2
ETH_RXD3: R510.1, U1.Y3
ETH_RXDV_CRS: R511.1, U1.V2
ETH_TXCLK: R506.1, U1.Y2
ETH_TXD0: R501.1, U1.AA1
ETH_TXD1: R502.1, U1.AA2
ETH_TXD2: R503.1, U1.AB3
ETH_TXD3: R504.1, U1.AB2
ETH_TXEN: R505.1, U1.AA3
EXP_GPIO0: J3.27, R8103.1, U1.K2, U8101.2
EXP_GPIO1: J3.28, R8102.1, U1.L3, U8101.6
EXP_GPIO2: J3.29, U1.K3
EXP_GPIO3: J3.30, U1.L2
EXP_I2C_SCL: J3.24, R2102.1, U1.AF16
EXP_I2C_SDA: J3.23, R2101.1, U1.AE15
EXP_SPI_CLK: J3.31, U1.AE16
EXP_SPI_CS0_N: J3.34, R2103.1, U1.AG17
EXP_SPI_CS1_N: J3.35, R2104.1, U1.AF15
EXP_SPI_MISO: J3.33, U1.AE18
EXP_SPI_MOSI: J3.32, U1.AG19
EXP_UART_RX: J3.26, U1.Y25
EXP_UART_TX: J3.25, U1.Y26
FLASH_CLK: R1401.2, U18.6
FSPI_CLK: R1401.1, U1.M25
FSPI_CS_N: R1402.1, U1.M26, U18.1
FSPI_D0: U1.J25, U18.5
FSPI_D1: U1.J26, U18.2
FSPI_D2: R1403.1, U1.H25, U18.3
FSPI_D3: R1404.1, U1.K27, U18.7
GND: C410.2, C411.2, C412.2, C413.2, C414.2, C415.2, C421.2, C422.2, C423.2, C424.2, C425.2, C431.2, C432.2, C433.2, C434.2, C435.2, C441.2, C442.2, C443.2, C444.2, C445.2, C460.2, C461.2, C462.2, C463.2, C464.2, C465.2, C466.2, C467.2, C468.2, C469.2, C470.2, C480.2, C481.2, C482.2, C483.2, C484.2, C485.2, C501.2, C511.2, C512.2, C513.2, C514.2, C515.2, C516.2, C517.2, C518.2, C519.2, C520.2, C521.2, C522.2, C531.2, C605.2, C606.2, C1001.2, C1002.2, C1011.2, C1012.2, C1013.2, C1014.2, C1101.2, C1102.2, C1103.2, C1104.2, C1105.2, C1106.2, C1107.2, C1201.2, C1202.2, C1203.2, C1301.2, C1302.2, C1303.2, C1304.2, C1305.2, C1401.2, C1402.2, C1501.2, C1502.2, C1503.2, C1601.2, C1602.2, C1603.2, C1604.2, C1605.2, C1606.2, C1607.2, C1608.2, C1609.2, C1610.2, C1611.2, C1612.2, C1613.2, C1614.2, C1615.2, C1616.2, C1617.2, C1618.2, C1619.2, C1620.2, C1621.2, C1622.2, C1623.2, C1624.2, C1625.2, C1626.2, C1627.2, C1628.2, C1629.2, C1630.2, C1631.2, C1632.2, C1633.2, C1634.2, C1635.2, C1636.2, C1637.2, C1638.2, C1639.2, C1640.2, C1641.2, C1642.2, C1643.2, C1644.2, C1645.2, C1646.2, C1647.2, C1648.2, C1649.2, C1650.2, C1651.2, C1652.2, C1653.2, C1654.2, C1655.2, C1656.2, C1657.2, C1658.2, C1659.2, C1660.2, C1661.2, C1662.2, C1663.2, C1664.2, C1665.2, C1666.2, C1667.2, C1668.2, C1669.2, C1670.2, C1671.2, C1672.2, C1673.2, C1674.2, C1675.2, C1676.2, C1677.2, C1678.2, C1679.2, C1680.2, C1681.2, C1682.2, C1683.2, C1801.2, C1802.2, C1811.2, C1812.2, C1901.2, C1902.2, C1903.2, C2001.2, C2002.2, C2003.2, C2004.2, C2005.2, C2006.2, C2007.2, C2008.2, C2009.2, C2201.2, C2202.2, C2203.2, C2204.2, C2301.2, C2302.2, C2303.2, C2304.2, C2305.2, C2306.2, C2307.2, C2308.2, C8101.2, C8102.2, C8103.2, J1.A1, J1.A12, J1.B1, J1.B12, J3.9, J3.10, J3.11, J3.12, J3.13, J3.14, J3.15, J3.16, J3.17, J3.18, J3.20, J3.22, J3.37, J3.38, J2001.2, J2001.3, Q1.2, R411.2, R432.2, R513.2, R516.2, R522.2, R523.2, R524.2, R528.2, R529.2, R1102.2, R1103.2, R1201.2, R1506.2, R1802.2, R1804.2, R1811.2, R1812.2, R1813.2, R1814.2, R1902.2, R1904.2, R1905.2, R2002.2, R2203.2, R8101.2, R8103.2, TP1.1, U1.1A2, U1.1A4, U1.1A5, U1.1A11, U1.1A12, U1.1A14, U1.1B2, U1.1B4, U1.1B5, U1.1B9, U1.1B12, U1.1B14, U1.1C1, U1.1C2, U1.1C3, U1.1C4, U1.1C5, U1.1C6, U1.1C7, U1.1C10, U1.1C11, U1.1C12, U1.1C13, U1.1C14, U1.1C15, U1.1D1, U1.1D2, U1.1D3, U1.1D7, U1.1D8, U1.1D9, U1.1D10, U1.1D12, U1.1D13, U1.1D14, U1.1D15, U1.1E1, U1.1E2, U1.1E11, U1.1E13, U1.1F1, U1.1F2, U1.1F3, U1.1F4, U1.1F5, U1.1F7, U1.1F9, U1.1F10, U1.1F15, U1.1G2, U1.1G6, U1.1G7, U1.1G9, U1.1G13, U1.1G14, U1.1H1, U1.1H2, U1.1H5, U1.1H9, U1.1H12, U1.1H13, U1.1J1, U1.1J2, U1.1J3, U1.1J4, U1.1J5, U1.1J8, U1.1J9, U1.1J13, U1.1K1, U1.1K4, U1.1K5, U1.1K6, U1.1K7, U1.1K8, U1.1K9, U1.1K11, U1.1K12, U1.1K13, U1.1L2, U1.1L4, U1.1L7, U1.1L9, U1.1L10, U1.1L15, U1.1M3, U1.1M5, U1.1M6, U1.1M12, U1.1N1, U1.1N2, U1.1N3, U1.1N4, U1.1N5, U1.1N6, U1.1N7, U1.1N8, U1.1N10, U1.1N11, U1.1N12, U1.1N13, U1.1N14, U1.1N15, U1.1P1, U1.1P2, U1.1P4, U1.1P5, U1.1P6, U1.1P8, U1.1P9, U1.1P10, U1.1P11, U1.1P13, U1.1R1, U1.1R2, U1.1R4, U1.1R5, U1.1R6, U1.1R8, U1.1R9, U1.1R10, U1.1R12, U1.1R14, U1.A1, U1.A12, U1.A16, U1.A27, U1.AA26, U1.AA27, U1.AB25, U1.AC3, U1.AD3, U1.AD25, U1.AE2, U1.AE3, U1.AE4, U1.AE5, U1.AE6, U1.AE7, U1.AE8, U1.AE9, U1.AE10, U1.AE11, U1.AE12, U1.AE13, U1.AE14, U1.AE21, U1.AE25, U1.AF24, U1.AG1, U1.AG15, U1.AG26, U1.AG27, U1.B14, U1.C3, U1.C4, U1.C7, U1.C9, U1.C13, U1.C14, U1.C15, U1.C19, U1.C21, U1.C24, U1.C25, U1.D2, U1.D25, U1.E3, U1.E25, U1.E26, U1.E27, U1.F3, U1.F25, U1.F26, U1.G25, U1.G26, U1.G27, U1.J3, U1.L25, U1.M27, U1.P26, U1.U3, U2.A3, U2.A10, U2.AB3, U2.AB5, U2.AB8, U2.AB10, U2.C1, U2.C5, U2.C8, U2.C12, U2.D2, U2.D4, U2.D9, U2.D11, U2.E1, U2.E5, U2.E8, U2.E12, U2.G1, U2.G3, U2.G5, U2.G8, U2.G10, U2.G12, U2.J1, U2.J3, U2.J10, U2.J12, U2.K2, U2.K4, U2.K9, U2.K11, U2.N2, U2.N4, U2.N9, U2.N11, U2.P1, U2.P3, U2.P10, U2.P12, U2.T1, U2.T3, U2.T5, U2.T8, U2.T10, U2.T12, U2.V1, U2.V5, U2.V8, U2.V12, U2.W2, U2.W4, U2.W9, U2.W11, U2.Y1, U2.Y5, U2.Y8, U2.Y12, U4.14, U4.15, U4.16, U4.17, U4.19, U4.40, U4.47, U4.56, U4.62, U4.63, U4.69, U5.41, U6.3, U6.4, U6.13, U6.28, U6.31, U7.3, U7.8, U8.3, U8.8, U9.3, U9.8, U10.B2, U10.B3, U10.B4, U10.C1, U10.C2, U10.C3, U10.C4, U11.2, U12.2, U13.3, U14.3, U15.8, U15.9, U16.3, U17.5, U17.6, U17.7, U17.8, U17.15, U17.16, U17.17, U18.4, U18.9, U19.3, U20.2, U21.1, U21.7, U21.8, U21.9, U21.10, U21.19, U22.3, U22.8, U23.3, U23.8, U24.1, U24.3, U24.16, U24.21, U25.1, U25.3, U25.6, U25.20, U25.26, U25.27, U25.28, U25.29, U25.31, U25.33, U25.34, U25.36, U25.43, U25.44, U26.6, U26.7, U26.8, U26.15, U26.16, U26.17, U8101.8, U8101.9, Y1.2, Y1.4, Y501.2, Y501.4, Y2001.2, Y2002.2, Y2002.4
I2C0_SCL: R414.1, R416.2, U1.AG23, U10.A3
I2C0_SDA: R415.1, R417.2, U1.AE23, U10.B1
LCD_BL_BASE: Q1.1, R1801.2, R1802.1
LCD_BL_PWM: R1801.1, U1.L1
LCD_CS_N: R1815.1, U1.M3, U21.6
LCD_DC: R1813.1, U1.N1, U21.4
LCD_MOSI: R1811.1, U1.T3, U21.2
LCD_RESET_N: R1814.1, U1.N2, U21.5
LCD_SCLK: R1812.1, U1.N3, U21.3
LPDDR4_A0_A: U1.B10, U2.H2
LPDDR4_A0_B: U1.B18, U2.R2
LPDDR4_A1_A: U1.A10, U2.J2
LPDDR4_A1_B: U1.A18, U2.P2
LPDDR4_A2_A: U1.C10, U2.H9
LPDDR4_A2_B: U1.C18, U2.R9
LPDDR4_A3_A: U1.1A6, U2.H10
LPDDR4_A3_B: U1.1A10, U2.R10
LPDDR4_A4_A: U1.1B8, U2.H11
LPDDR4_A4_B: U1.1A9, U2.R11
LPDDR4_A5_A: U1.1A7, U2.J11
LPDDR4_A5_B: U1.1A8, U2.P11
LPDDR4_CKE0_A: U1.C12, U2.J4
LPDDR4_CKE0_B: U1.C16, U2.P4
LPDDR4_CLKN_A: U1.A13, U2.J9
LPDDR4_CLKN_B: U1.A15, U2.P9
LPDDR4_CLKP_A: U1.B13, U2.J8
LPDDR4_CLKP_B: U1.B15, U2.P8
LPDDR4_CS0N_A: U1.B11, U2.H4
LPDDR4_CS0N_B: U1.B17, U2.R4
LPDDR4_DM0_A: U1.B7, U2.C3
LPDDR4_DM0_B: U1.B21, U2.Y3
LPDDR4_DM1_A: U1.A2, U2.C10
LPDDR4_DM1_B: U1.A26, U2.Y10
LPDDR4_DQ0_A: U1.B6, U2.B2
LPDDR4_DQ0_B: U1.B22, U2.AA2
LPDDR4_DQ1_A: U1.B8, U2.C2
LPDDR4_DQ1_B: U1.B20, U2.Y2
LPDDR4_DQ2_A: U1.A8, U2.E2
LPDDR4_DQ2_B: U1.A20, U2.V2
LPDDR4_DQ3_A: U1.C8, U2.F2
LPDDR4_DQ3_B: U1.C20, U2.U2
LPDDR4_DQ4_A: U1.C5, U2.F4
LPDDR4_DQ4_B: U1.C23, U2.U4
LPDDR4_DQ5_A: U1.B5, U2.E4
LPDDR4_DQ5_B: U1.B23, U2.V4
LPDDR4_DQ6_A: U1.A6, U2.C4
LPDDR4_DQ6_B: U1.C22, U2.Y4
LPDDR4_DQ7_A: U1.C6, U2.B4
LPDDR4_DQ7_B: U1.A22, U2.AA4
LPDDR4_DQ8_A: U1.C2, U2.B11
LPDDR4_DQ8_B: U1.C26, U2.AA11
LPDDR4_DQ9_A: U1.C1, U2.C11
LPDDR4_DQ9_B: U1.C27, U2.Y11
LPDDR4_DQ10_A: U1.B1, U2.E11
LPDDR4_DQ10_B: U1.B27, U2.V11
LPDDR4_DQ11_A: U1.B2, U2.F11
LPDDR4_DQ11_B: U1.B26, U2.U11
LPDDR4_DQ12_A: U1.A4, U2.F9
LPDDR4_DQ12_B: U1.A24, U2.U9
LPDDR4_DQ13_A: U1.B4, U2.E9
LPDDR4_DQ13_B: U1.B24, U2.V9
LPDDR4_DQ14_A: U1.A3, U2.C9
LPDDR4_DQ14_B: U1.A25, U2.Y9
LPDDR4_DQ15_A: U1.B3, U2.B9
LPDDR4_DQ15_B: U1.B25, U2.AA9
LPDDR4_DQS0N_A: U1.1B3, U2.E3
LPDDR4_DQS0N_B: U1.1B13, U2.V3
LPDDR4_DQS0P_A: U1.1A3, U2.D3
LPDDR4_DQS0P_B: U1.1A13, U2.W3
LPDDR4_DQS1N_A: U1.1B1, U2.E10
LPDDR4_DQS1N_B: U1.1B15, U2.V10
LPDDR4_DQS1P_A: U1.1A1, U2.D10
LPDDR4_DQS1P_B: U1.1A15, U2.W10
LPDDR4_RESETN: U1.1B11, U2.T11
LPDDR4_ZQ_240R: R201.1, U2.A5
MUX_TX1_N: C602.1, U6.16
MUX_TX1_P: C601.1, U6.17
MUX_TX2_N: C604.1, U6.20
MUX_TX2_P: C603.1, U6.21
PHY_CFG_EXT: R527.1, U5.32
PHY_CFG_LDO0: R528.1, U5.33
PHY_CFG_LDO1: R529.1, U5.34
PHY_RESET_N: C501.1, R515.2, R516.1, U5.12
PHY_RSET: R513.1, U5.39
PHY_RXCLK: R512.2, R522.1, U5.27
PHY_RXD0: R507.2, R526.1, U5.25
PHY_RXD1: R508.2, R525.1, U5.24
PHY_RXD2: R509.2, R524.1, U5.23
PHY_RXD3: R510.2, R521.1, U5.22
PHY_RXDV_CRS: R511.2, R523.1, U5.26
PHY_SW: L501.1, U5.30
PHY_TXCLK: R506.2, U5.20
PHY_TXD0: R501.2, U5.18
PHY_TXD1: R502.2, U5.17
PHY_TXD2: R503.2, U5.16
PHY_TXD3: R504.2, U5.15
PHY_TXEN: R505.2, U5.19
PHY_XIN: C520.1, U5.36, Y501.1
PHY_XOUT: C521.1, U5.37, Y501.3
PMIC_1V8A: C414.1, U4.44
PMIC_1V8D: C415.1, U4.48
PMIC_INT_N: R413.2, U1.AF22, U4.7
PMIC_PWRON_N: C412.1, U4.52
PMIC_SCL: R414.2, U4.1
PMIC_SDA: R415.2, U4.2
PMIC_SLEEP: U1.AF23, U4.49, U10.A1
PMIC_SW1: L401.1, U4.12
PMIC_SW2: L402.1, U4.9
PMIC_SW3: L403.1, U4.25
PMIC_SW4: L404.1, U4.65
PMIC_SW5: L405.1, U4.53
PMIC_VDC: C410.1, R410.2, R411.1, U4.61
PMIC_VREF: C413.1, U4.46
RECOVERY_ADC: R1504.1, TP10.1, U1.D26
RESET_N: C411.1, R412.2, R1103.1, R1507.2, TP9.1, U1.1P12, U4.67, U16.2
SOC_USB_RX_N: U1.AB27, U6.10
SOC_USB_RX_P: U1.AB26, U6.9
SOC_USB_TX_N: U1.AD27, U6.7
SOC_USB_TX_P: U1.AD26, U6.6
SOC_VBUS_DET: C1503.1, R1505.2, R1506.1, U1.1P14
SYS_3V3_PG: R1301.1, TP14.1, U17.4
SYS_SS: C1303.1, U17.9
SYS_SW: L1301.1, U17.1, U17.2, U17.3
THERMAL_SHUTDOWN: R1507.1, U1.1R13
USB_AVDD_0V9: C1679.1, C1680.1, R1601.2, U1.1L14
USB_AVDD_1V8: C1681.1, C1682.1, R1602.2, U1.1M15
USB_CC1: J1.A5, U6.2, U9.4
USB_CC2: J1.B5, U6.1, U9.5
USB_CC_ENABLE_N: U6.29, U13.4
USB_CURRENT_OK: U14.4, U19.1
USB_DM: J1.A7, J1.B7, U1.AF26, U9.2
USB_DP: J1.A6, J1.B6, U1.AF27, U9.1
USB_DVDT: C1202.1, U15.1
USB_ILIM: R1201.1, U15.7
USB_MAIN_ENABLE: R1102.1, U15.2, U19.4
USB_MUX_ENABLE_N: U6.12, U16.4
USB_ORIENTATION: R602.2, U6.11
USB_POWER_FAULT_N: R1202.1, TP13.1, U15.6
USB_RX1_N: J1.B10, U6.14, U7.5
USB_RX1_P: J1.B11, U6.15, U7.4
USB_RX2_N: J1.A10, U6.18, U8.5
USB_RX2_P: J1.A11, U6.19, U8.4
USB_TX1_N: C602.2, J1.A3, U7.2
USB_TX1_P: C601.2, J1.A2, U7.1
USB_TX2_N: C604.2, J1.B3, U8.2
USB_TX2_P: C603.2, J1.B2, U8.1
VBUS_GUARD_DVDT: C1903.1, U24.18
VBUS_GUARD_ILIM: R1905.1, U24.17
VBUS_OVP: R1903.2, R1904.1, U24.15
VBUS_PROTECTED: C605.1, C1101.1, C1201.1, C1902.1, R601.1, U6.30, U11.1, U11.3, U15.3, U15.4, U24.4, U24.5, U24.6, U24.7, U24.8
VBUS_RAW: C1901.1, J1.A4, J1.A9, J1.B4, J1.B9, R1901.1, R1903.1, TP2.1, U24.9, U24.10, U24.11, U24.12, U24.13
VBUS_UVLO: R1901.2, R1902.1, U24.14
VCCA1V8_IMAGE: C468.1, U1.1M7, U1.1M8, U1.1N9, U4.6
VCCA1V8_PMU: C467.1, C1631.1, C1632.1, U1.1L13, U4.5
VCCA_1V8: C466.1, C1635.1, C1636.1, C1644.1, C1645.1, R1504.2, R1602.1, U1.1E14, U1.1E15, U1.1G1, U1.1K2, U1.1K15, U4.3
VCCIO_ACODEC: C463.1, U4.28
VCCIO_SD: C464.1, U4.29
VDDA0V9_IMAGE: C460.1, U1.1L6, U1.1L8, U1.1M9, U4.23
VDDA0V9_PMU: C462.1, C1629.1, C1630.1, U1.1M11, U1.1M13, U4.20
VDDA_0V9: C461.1, C1633.1, C1634.1, C1642.1, C1643.1, R1601.1, U1.1K14, U1.1M10, U4.21
VDD_CPU: C1011.1, C1012.1, C1013.1, C1014.1, C1020.1, C1601.1, C1602.1, C1603.1, C1604.1, C1605.1, C1606.1, C1607.1, C1608.1, L1001.2, R1001.1, TP8.1, U1.1G8, U1.1H6, U1.1H7, U1.1H8, U1.1J6, U1.1J7
VDD_GPU: C432.1, C442.1, C452.1, C1616.1, C1617.1, C1618.1, C1619.1, C1620.1, L402.2, R422.1, U1.1E12, U1.1F11, U1.1F12, U1.1F13, U1.1G11, U1.1G12
VDD_GPU_COM: C452.2, R422.2, U4.8
VDD_LOGIC: C431.1, C441.1, C451.1, C1609.1, C1610.1, C1611.1, C1612.1, C1613.1, C1614.1, C1615.1, L401.2, R421.1, U1.1G10, U1.1H10, U1.1H11, U1.1J10, U1.1J11, U1.1J12, U1.1K10
VDD_LOGIC_COM: C451.2, R421.2, U4.13
VDD_NPU: C434.1, C444.1, C454.1, C1621.1, C1622.1, C1623.1, C1624.1, L404.2, R424.1, U1.1G3, U1.1G4, U1.1G5, U1.1H3, U1.1H4
VDD_NPU_COM: C454.2, R424.2, U4.64
WIFI_ANT: J2001.1, R2001.2
WIFI_BUCK_OUT: C2003.1, L2001.2, U25.23
WIFI_BUCK_SW: L2001.1, U25.21
WIFI_CLK: U1.U25, U25.17
WIFI_CMD: R2014.1, U1.T27, U25.16
WIFI_D0: R2010.1, U1.U26, U25.18
WIFI_D1: R2011.1, U1.V25, U25.19
WIFI_D2: R2012.1, U1.T25, U25.14
WIFI_D3: R2013.1, U1.T26, U25.15
WIFI_HOST_WAKE: U1.V26, U25.13
WIFI_LPO: R2003.2, U25.24
WIFI_LPO_SRC: R2003.1, Y2001.3
WIFI_REG_ON: R2002.1, U1.1J14, U25.12
WIFI_RF: R2001.1, U25.2
WIFI_VBAT: C2001.1, C2002.1, FB2001.2, U25.9
WIFI_VBAT_FB: R2202.2, R2203.1, U26.5
WIFI_VBAT_PG: R2201.1, U17.13, U26.4
WIFI_VBAT_SS: C2203.1, U26.9
WIFI_VBAT_SW: L2201.1, U26.1, U26.2, U26.3
WIFI_XIN: C2008.1, U25.10, Y2002.1
WIFI_XOUT: R2004.1, U25.11
WIFI_XTAL_OUT: C2009.1, R2004.2, Y2002.3
XIN24M: C1501.1, R1502.2, U1.AG25, Y1.1
XOUT24M: R1501.1, R1502.1, U1.AF25
XTAL24_DRIVE: C1502.1, R1501.2, Y1.3
